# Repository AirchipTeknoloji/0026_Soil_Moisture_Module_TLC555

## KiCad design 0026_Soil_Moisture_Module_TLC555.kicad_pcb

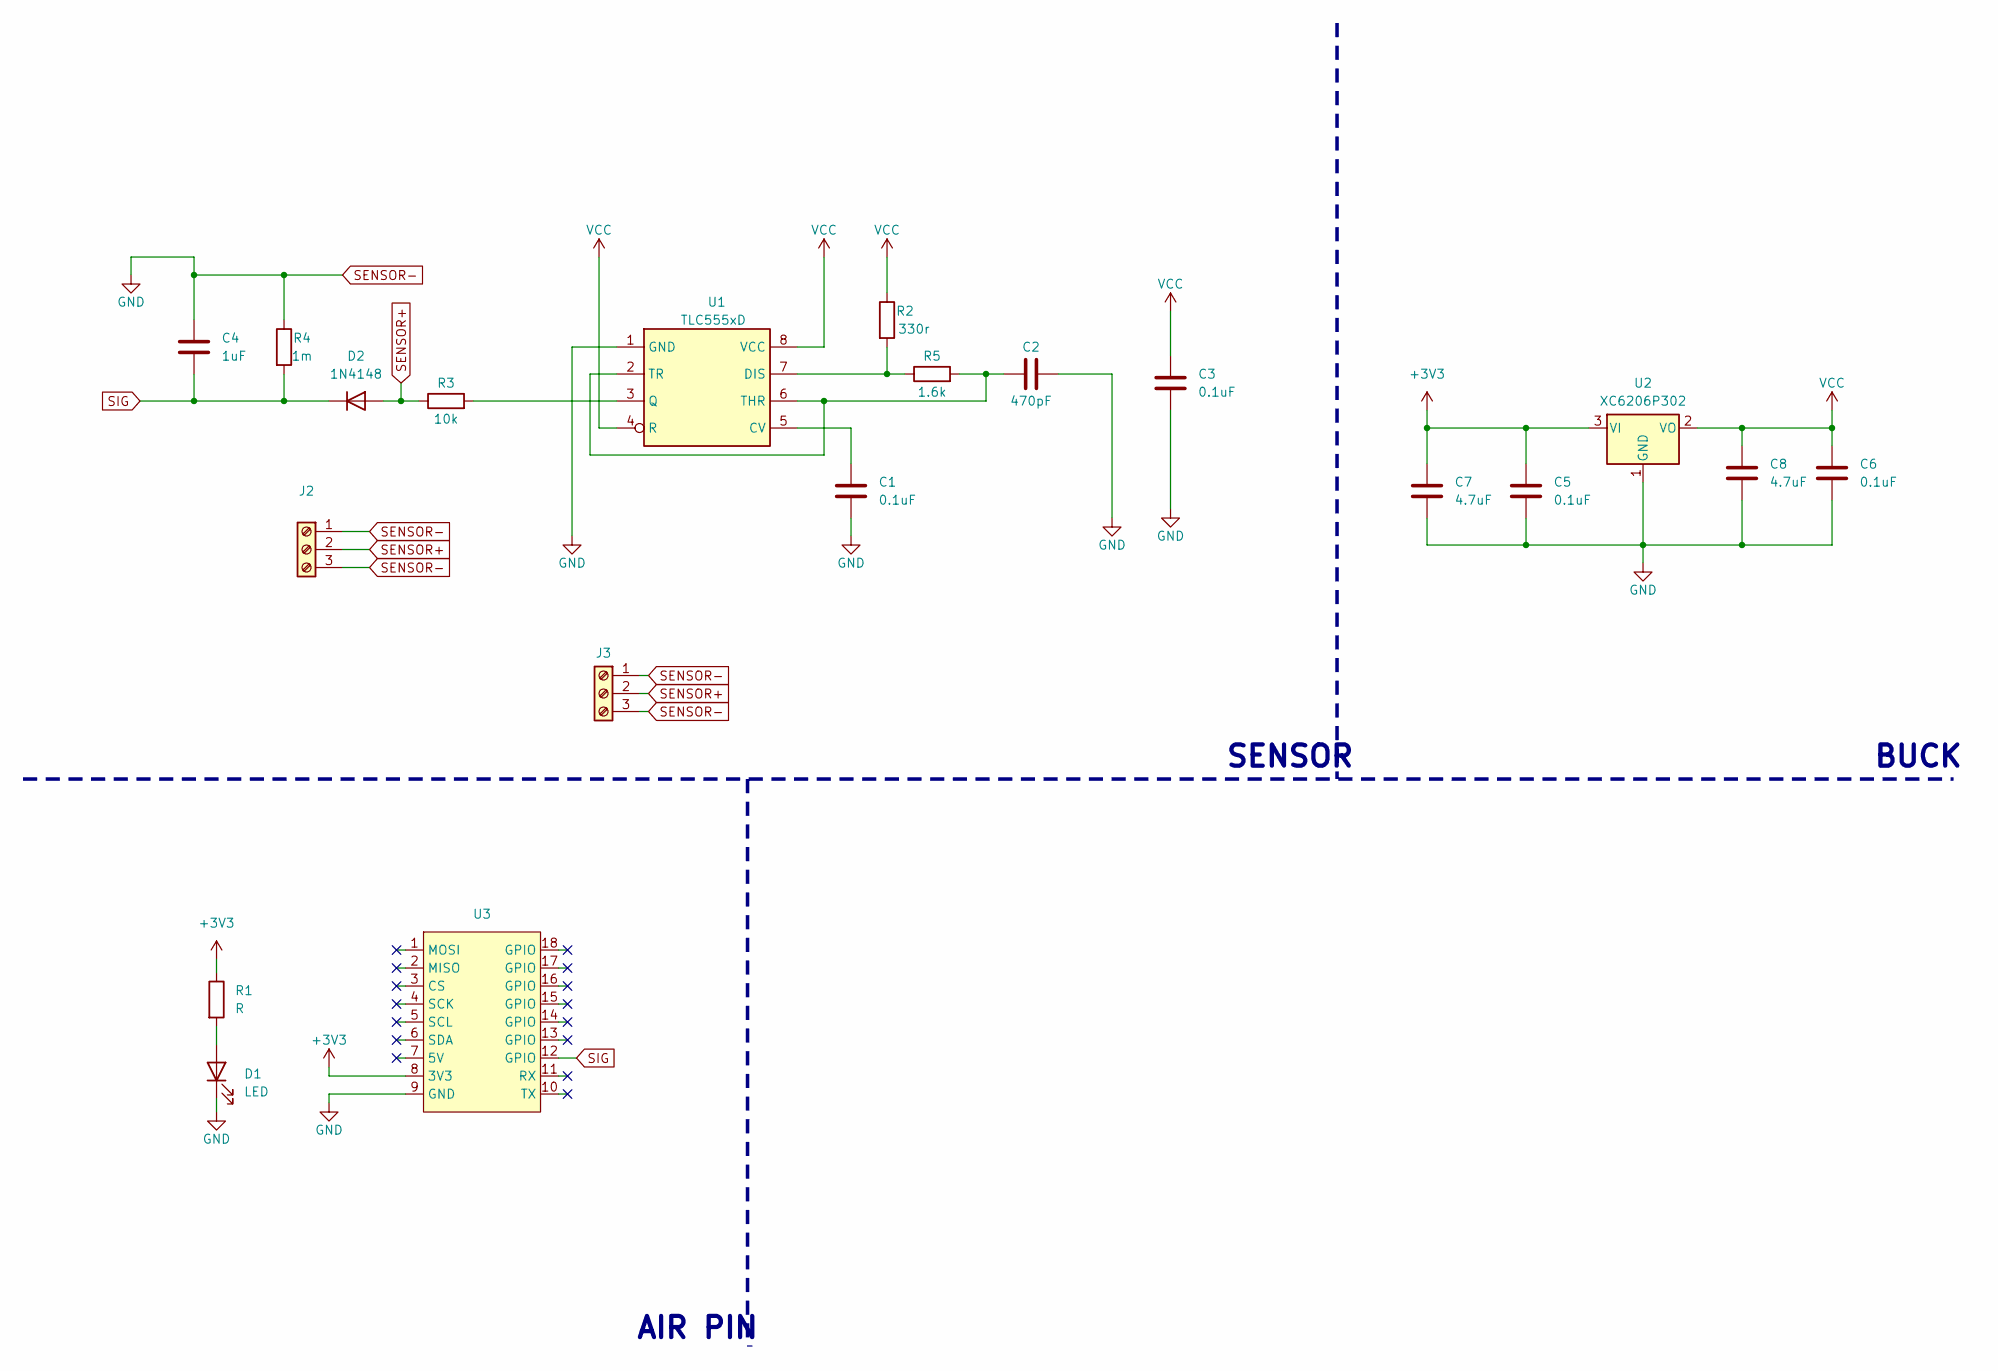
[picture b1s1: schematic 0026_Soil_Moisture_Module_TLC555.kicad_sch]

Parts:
C1, C3, C5, C6: 0.1uF; C_0603_1608Metric
C2: 470pF; C_0603_1608Metric
C4: 1uF; C_0603_1608Metric
C7, C8: 4.7uF; C_0603_1608Metric
D1: LED; LED_0603_1608Metric
D2: 1N4148; D_0805_2012Metric
J2, J3: Screw_Terminal_01x03; TerminalBlock_4Ucon_1x03_P3.50mm_Horizontal
R1: R; R_0603_1608Metric
R2: 330r; R_0603_1608Metric
R3: 10k; R_0603_1608Metric
R4: 1m; R_0603_1608Metric
R5: 1.6k; R_0603_1608Metric
U1: TLC555xD; SOIC-8_3.9x4.9mm_P1.27mm
U2: XC6206P302; SOT-23-3
U3: air_module

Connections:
+3V3: C5.1, C7.1, R1.1, U2.3 (VI), U3.8 (3V3)
unnamed: D1.2 (A), R1.2
unnamed: C1.1, U1.5 (CV)
unnamed: R2.2, R5.1, U1.7 (DIS)
unnamed: R3.2, U1.3 (Q)
unnamed: C2.1, R5.2, U1.2 (TR), U1.6 (THR)
SENSOR+: D2.2 (A), J2.2, J3.2, R3.1
SENSOR-: C1.2, C2.2, C3.1, C4.1, C5.2, C6.2, C7.2, C8.2, D1.1 (K), J2.1, J2.3, J3.1, J3.3, R4.1, U1.1 (GND), U2.1 (GND), U3.9 (GND)
SIG: C4.2, D2.1 (K), R4.2, U3.12 (GPIO)
VCC: C3.2, C6.1, C8.1, R2.1, U1.4 (R), U1.8 (VCC), U2.2 (VO)

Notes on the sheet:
BUCK
SENSOR
AIR PIN

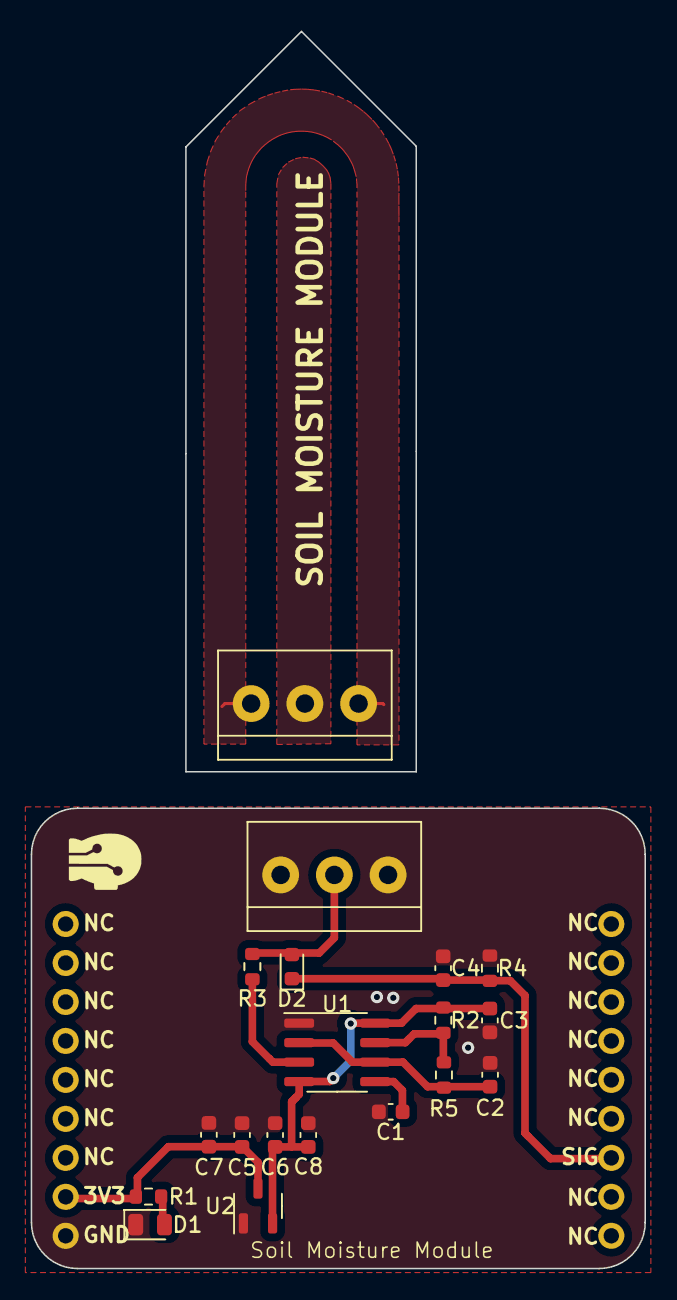
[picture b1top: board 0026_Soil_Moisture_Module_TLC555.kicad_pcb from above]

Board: 2 copper layers, 40.0 x 80.6 mm, 20 parts (0 on the bottom side), 10 nets.
